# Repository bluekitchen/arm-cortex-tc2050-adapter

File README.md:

# ARM Cortex Tag-Connect 2050 Adapter

A simple adapter to connect development boards with a 10-pin Tag Connect connector to a JTAG/SWD tool like SEGGER's J-Link.

The adapter can be directly plugged into the [20-pin JTAG interface](https://www.segger.com/products/debug-probes/j-link/technology/interface-description/). On the other side, the [TC-2050-IDC](https://www.tag-connect.com/TC2050-IDC) can be plugged in.

It is can be directly [ordered at OSHpark](https://oshpark.com/shared_projects/WIUZbvZ1)

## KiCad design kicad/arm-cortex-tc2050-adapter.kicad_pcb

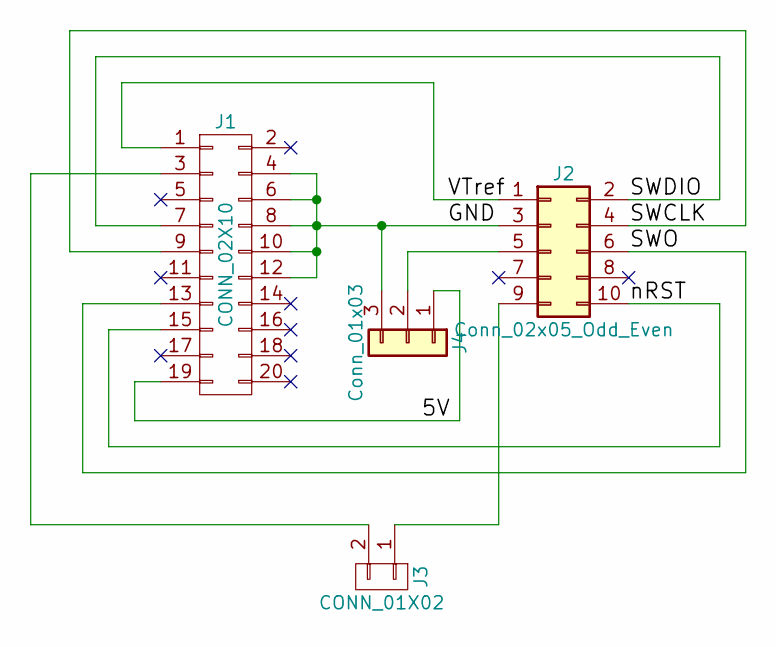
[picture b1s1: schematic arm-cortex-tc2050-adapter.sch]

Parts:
J1: CONN_02X10; IDC_Header_Straight_20pins
J2: Conn_02x05_Odd_Even; Pin_Header_Straight_2x05
J3: CONN_01X02; Socket_Strip_Straight_1x02
J4: Conn_01x03; Socket_Strip_Straight_1x03

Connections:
/5V: J1.19, J4.1
/GND: J1.4, J1.6, J1.8, J1.10, J1.12, J2.3, J4.3
/SWCLK: J1.9, J2.4
/SWDIO: J1.7, J2.2
/SWO: J1.13, J2.6
/VTref: J1.1, J2.1
/nRST: J1.15, J2.10
unnamed: J1.3, J3.2
unnamed: J2.5, J4.2
unnamed: J2.9, J3.1

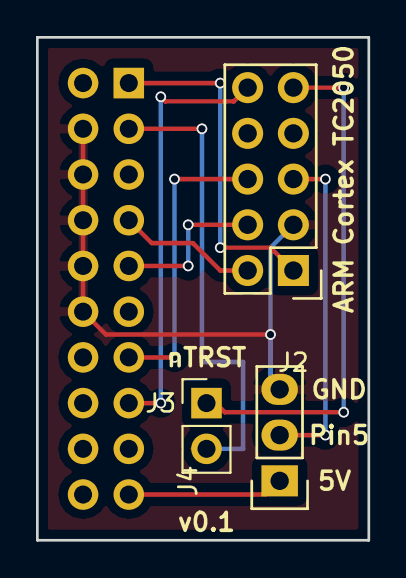
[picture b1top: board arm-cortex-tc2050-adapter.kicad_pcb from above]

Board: 2 copper layers, 18.4 x 27.9 mm, 4 parts (1 on the bottom side), 10 nets.

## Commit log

2018-09-07 add picture
2020-05-19 add schematic
